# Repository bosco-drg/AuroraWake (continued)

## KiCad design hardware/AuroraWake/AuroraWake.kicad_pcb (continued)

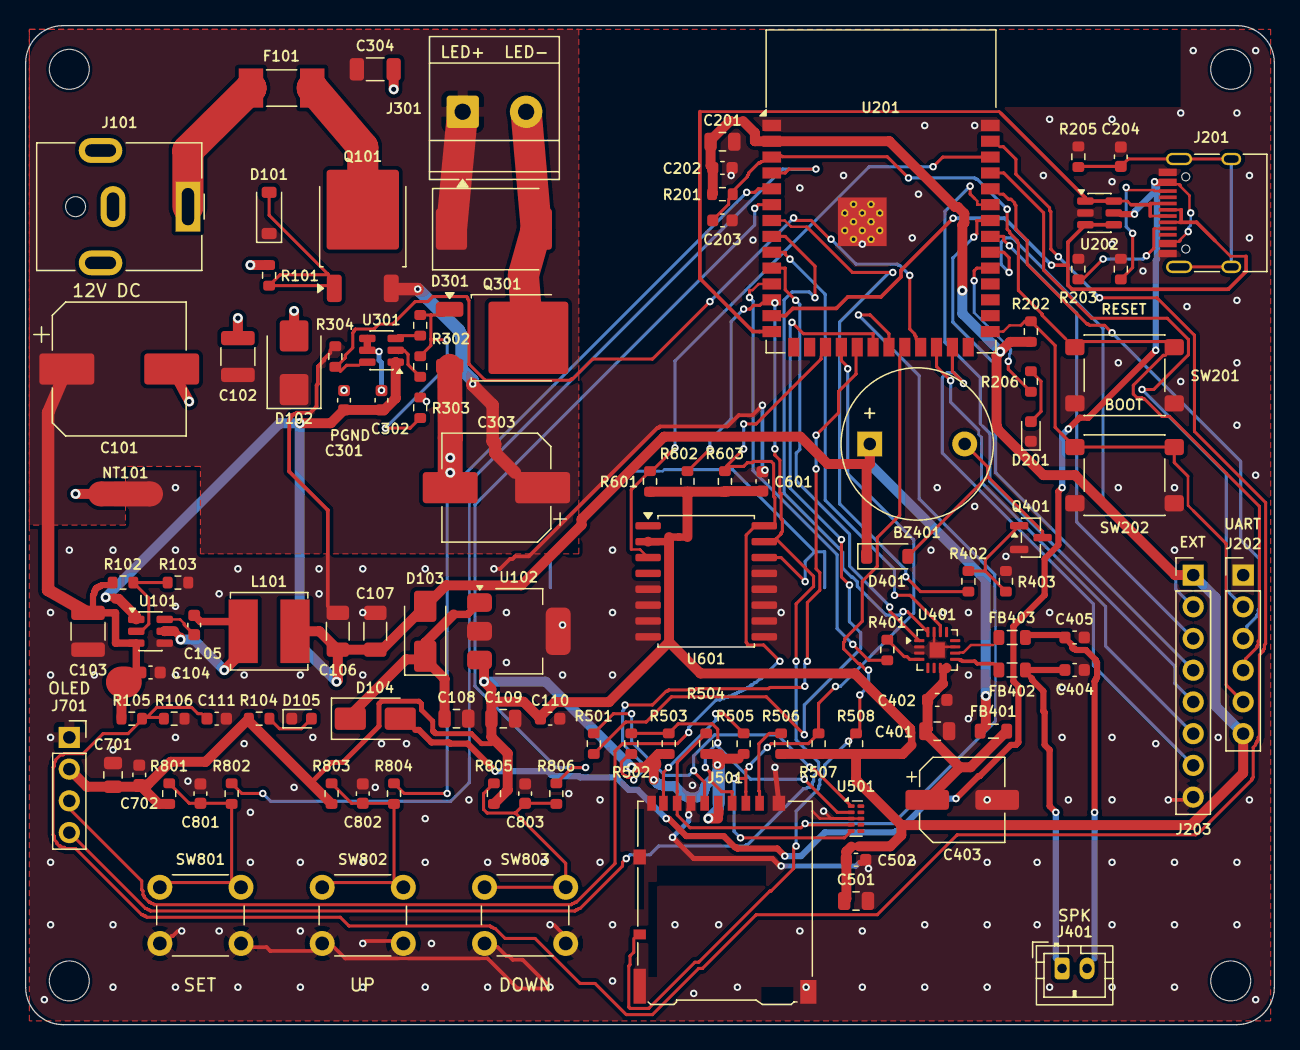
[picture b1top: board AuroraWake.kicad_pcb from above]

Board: 2 copper layers, 100.0 x 80.0 mm, 112 parts (1 on the bottom side), 69 nets.

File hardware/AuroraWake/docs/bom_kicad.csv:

"Reference","Value","Footprint","MPN","QUANTITY"
"BT601","CR2032","Battery:BatteryHolder_Keystone_3034_1x20mm","Keystone 3034","1"
"BZ401","Buzzer passif 5V","Buzzer_Beeper:Buzzer_12x9.5RM7.6","","1"
"C101","470uF 35V","Capacitor_SMD:CP_Elec_10x10.5","","1"
"C102,C103","10uF 35V X7R","Capacitor_SMD:C_1210_3225Metric","","2"
"C104","100nF 50V","Capacitor_SMD:C_0603_1608Metric","","1"
"C105,C110,C111,C202,C302,C402,C502,C601,C702,C801,C802,C803","100nF","Capacitor_SMD:C_0603_1608Metric","","12"
"C106,C107","22uF 10V X5R","Capacitor_SMD:C_1206_3216Metric","","2"
"C108,C109","10uF 16V","Capacitor_SMD:C_0805_2012Metric","","2"
"C201","22uF 10V","Capacitor_SMD:C_0805_2012Metric","","1"
"C203,C301","1uF","Capacitor_SMD:C_0603_1608Metric","","2"
"C204","4.7nF 100V","Capacitor_SMD:C_0603_1608Metric","","1"
"C303","100uF 35V","Capacitor_SMD:CP_Elec_8x10.5","","1"
"C304","1uF 50V X7R","Capacitor_SMD:C_1206_3216Metric","","1"
"C401,C501,C701","10uF 10V","Capacitor_SMD:C_0805_2012Metric","","3"
"C403","100uF 16V","Capacitor_SMD:CP_Elec_6.3x5.4","","1"
"C404,C405","1nF","Capacitor_SMD:C_0603_1608Metric","","2"
"D101","BZT52C15","Diode_SMD:D_SOD-123","","1"
"D102","SMBJ15A","Diode_SMD:D_SMB","SMBJ15A (TVS unidirectionnelle 600 W)","1"
"D103,D104","SS34","Diode_SMD:D_SMA","","2"
"D105","Vert","LED_SMD:LED_0603_1608Metric","","1"
"D201","Bleu","LED_SMD:LED_0603_1608Metric","","1"
"D301","SS54","Diode_SMD:D_SMC","SS54 (5 A 40 V)","1"
"D401","1N4148W","Diode_SMD:D_SOD-123","","1"
"F101","7A rapide NANO2","Fuse:Fuse_Littelfuse-NANO2-451_453","Littelfuse 0451007.MRL (NANO2 451, 7 A, 125 V)","1"
"FB401","600R@100MHz 2A","Inductor_SMD:L_0805_2012Metric","","1"
"FB402,FB403","220R@100MHz 2A","Inductor_SMD:L_0805_2012Metric","","2"
"H1,H2,H3,H4","M3","MountingHole:MountingHole_3.2mm_M3","","4"
"J101","Jack 12V 8A (PJ-063AH)","Connector_BarrelJack:BarrelJack_CUI_PJ-063AH_Horizontal","CUI PJ-063AH","1"
"J201","USB-C (prog/debug)","Connector_USB:USB_C_Receptacle_HRO_TYPE-C-31-M-12","HRO TYPE-C-31-M-12","1"
"J202","UART0 / prog","Connector_PinHeader_2.54mm:PinHeader_1x06_P2.54mm_Vertical","","1"
"J203","Extension / JTAG","Connector_PinHeader_2.54mm:PinHeader_1x08_P2.54mm_Vertical","","1"
"J301","Panneau LED 12V <=50W","TerminalBlock_Phoenix:TerminalBlock_Phoenix_MKDS-3-2-5.08_1x02_P5.08mm_Horizontal","Bornier 5,08 mm >= 15 A","1"
"J401","HP 4-8 Ohm 3W","Connector_JST:JST_PH_B2B-PH-K_1x02_P2.00mm_Vertical","","1"
"J501","microSD Hirose DM3AT","Connector_Card:microSD_HC_Hirose_DM3AT-SF-PEJM5","Hirose DM3AT-SF-PEJM5","1"
"J701","OLED SSD1306 128x64 0x3C","Connector_PinSocket_2.54mm:PinSocket_1x04_P2.54mm_Vertical","","1"
"L101","4.7uH 3.5A","Inductor_SMD:L_Bourns_SRN6045TA","Bourns SRN6045TA-4R7M (Isat >= 3,5 A)","1"
"NT101","NetTie PGND-GND","NetTie:NetTie-2_SMD_Pad2.0mm","","1"
"Q101","AOD4185","Package_TO_SOT_SMD:TO-252-2","AOD4185 (P-MOS -40V -40A, ~15mOhm)","1"
"Q301","AOD4184A","Package_TO_SOT_SMD:TO-252-2","AOD4184A (N-MOS 40V 50A)","1"
"Q401","AO3400A","Package_TO_SOT_SMD:SOT-23","","1"
"R101,R201,R202,R303,R401,R503,R504,R505,R506,R507,R508,R601,R801,R803,R805","10k","Resistor_SMD:R_0603_1608Metric","","15"
"R102,R105,R304,R403","100k","Resistor_SMD:R_0603_1608Metric","","4"
"R103,R106","15k","Resistor_SMD:R_0603_1608Metric","","2"
"R104,R206,R802,R804,R806","1k","Resistor_SMD:R_0603_1608Metric","","5"
"R203,R204","5.1k","Resistor_SMD:R_0603_1608Metric","","2"
"R205","1M","Resistor_SMD:R_0603_1608Metric","","1"
"R301","10R","Resistor_SMD:R_0603_1608Metric","","1"
"R302","4.7R","Resistor_SMD:R_0603_1608Metric","","1"
"R402","100R","Resistor_SMD:R_0603_1608Metric","","1"
"R501,R502","22R","Resistor_SMD:R_0603_1608Metric","","2"
"R602,R603","4.7k","Resistor_SMD:R_0603_1608Metric","","2"
"SW201","RESET","Button_Switch_SMD:SW_SPST_PTS645Sx43SMTR92","","1"
"SW202","BOOT","Button_Switch_SMD:SW_SPST_PTS645Sx43SMTR92","","1"
"SW801","MODE/OK","Button_Switch_THT:SW_PUSH_6mm_H8mm","","1"
"SW802","+","Button_Switch_THT:SW_PUSH_6mm_H8mm","","1"
"SW803","-","Button_Switch_THT:SW_PUSH_6mm_H8mm","","1"
"U101","AP63205WU-7","Package_TO_SOT_SMD:TSOT-23-6","Diodes AP63205WU-7","1"
"U102","AP7361C-33E","Package_TO_SOT_SMD:SOT-223-3_TabPin2","Diodes AP7361C-33E-13","1"
"U201","ESP32-S3-WROOM-1-N16R8","RF_Module:ESP32-S3-WROOM-1","Espressif ESP32-S3-WROOM-1-N16R8","1"
"U202","USBLC6-2SC6","Package_TO_SOT_SMD:SOT-23-6","","1"
"U301","UCC27511ADBVR","Package_TO_SOT_SMD:SOT-23-6","TI UCC27511ADBVR","1"
"U401","MAX98357AETE+T","Package_DFN_QFN:TQFN-16-1EP_3x3mm_P0.5mm_EP1.23x1.23mm","Analog Devices MAX98357AETE+T","1"
"U501","TPD4E05U06DQAR","Package_SON:USON-10_2.5x1.0mm_P0.5mm","","1"
"U601","DS3231SN#","Package_SO:SOIC-16W_7.5x10.3mm_P1.27mm","Analog Devices DS3231SN#","1"
